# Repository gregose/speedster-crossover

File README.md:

# Speedster Crossover

Crossover PCB layout for [Paul Carmody's Speedster speakers](https://sites.google.com/site/undefinition/speedster). Designed with V-cut stackable boards for high and low-pass circuits.

### Render

### Schematic

### BOM

The layout was designed for the following components. Extra pads have been added to allow the use of physically smaller capacitors. Additional pins have been added to X1 and X2 to support the use of through-hole quick disconnects.

Ref | Component | Link 
----| --------- | -------------
R1  | Vishay Mills MRA-12 10R | http://www.digikey.com/product-search/en?mpart=MRA-1210R00FE12&vendor=541
R2  | Vishay Mills MRA-12 8R | http://www.digikey.com/product-search/en?mpart=MRA-128R000FE12&vendor=541
C1  | AUDYN CAP PLUS MKP 2.20 MF/ 800 V 2% AXIAL 43X25 | https://www.intertechnik.com/Shop/Cross-over-parts/Capacitors/Audyn-Cap-Plus/_PLUS22008_1768,en,280,46735
C2  | AUDYN CAP PLUS MKP 4.70 MF/ 800 V 2% AXIAL 63X35 | https://www.intertechnik.com/Shop/Cross-over-parts/Capacitors/Audyn-Cap-Plus/_PLUS47008_1768,en,280,46738
C3  | AUDYN CAP PLUS MKP 4.70 MF/ 800 V 2% AXIAL 63X35 | https://www.intertechnik.com/Shop/Cross-over-parts/Capacitors/Audyn-Cap-Plus/_PLUS47008_1768,en,280,46738
L1  | Meniscus Audio .25mH, Perfect Layer 20ga. | http://meniscusaudio.com/025mh-20ga-p-597.html
L2  | Meniscus Audio 1.5mH, Layer  Wound 18ga. | http://meniscusaudio.com/150mh-18-ga-p-638.html
L3  | Meniscus Audio .35mH, Layer  Wound 18ga. | http://meniscusaudio.com/035mh-18-ga-p-622.html
X1  | Phoenix Contact 1730418 (CONN TERM BLOCK 4POS 5.08MM) | http://www.digikey.com/product-search/en?mpart=1730418&vendor=277
X2  | Phoenix Contact 1730434 (CONN TERM BLOCK 6POS 5.08MM) | http://www.digikey.com/product-search/en?mpart=1730434&vendor=277
X1/2 Alt. | PCB quick disconnect terminal | http://www.mcmaster.com/#7956k5/=10cwxu4

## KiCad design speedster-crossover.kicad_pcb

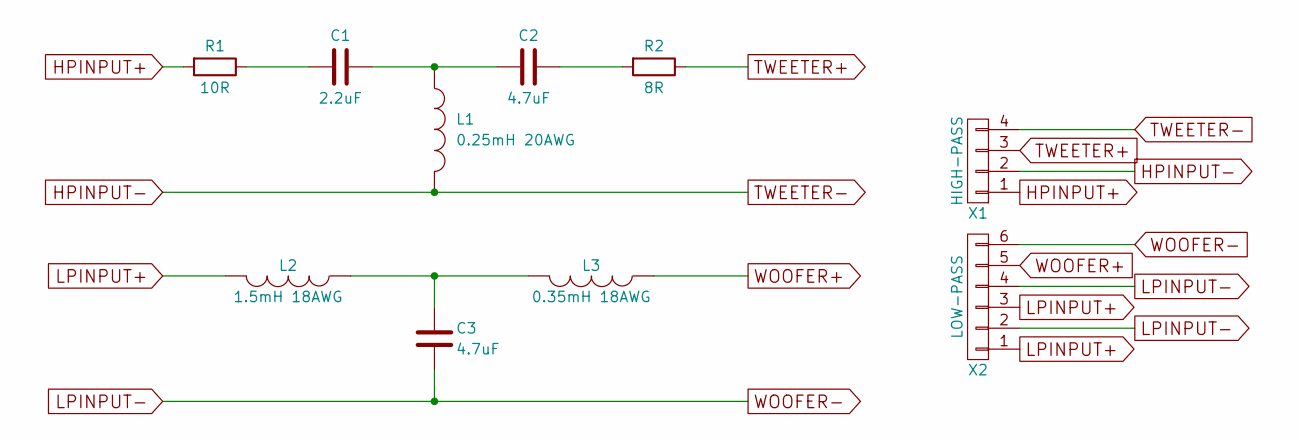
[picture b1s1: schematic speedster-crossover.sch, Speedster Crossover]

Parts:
C1: 2.2uF; OAL_cap_2.2
C2, C3: 4.7uF; OAL_cap_4.7
L1: 0.25mH 20AWG; OAL_inductor_0.25-20AWG-Vertical
L2: 1.5mH 18AWG; OAL_inductor_1.5-18AWG
L3: 0.35mH 18AWG; OAL_inductor_0.35-18AWG-Vertical
R1: 10R; OAL_resistor_MRA12
R2: 8R; OAL_resistor_MRA12
X1: HIGH-PASS; OAL_pheonix_mkds_2.5-4pos
X2: LOW-PASS; OAL_pheonix_mkds_2.5-6pos

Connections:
HPINPUT+: R1.2, X1.1
HPINPUT-: L1.2, X1.2, X1.4
LPINPUT+: L2.2, X2.1, X2.3
LPINPUT-: C3.2, X2.2, X2.4, X2.6
unnamed: C1.1, C2.1, L1.1
unnamed: C1.2, R1.1
unnamed: C2.2, R2.2
unnamed: C3.1, L2.1, L3.2
TWEETER+: R2.1, X1.3
WOOFER+: L3.1, X2.5

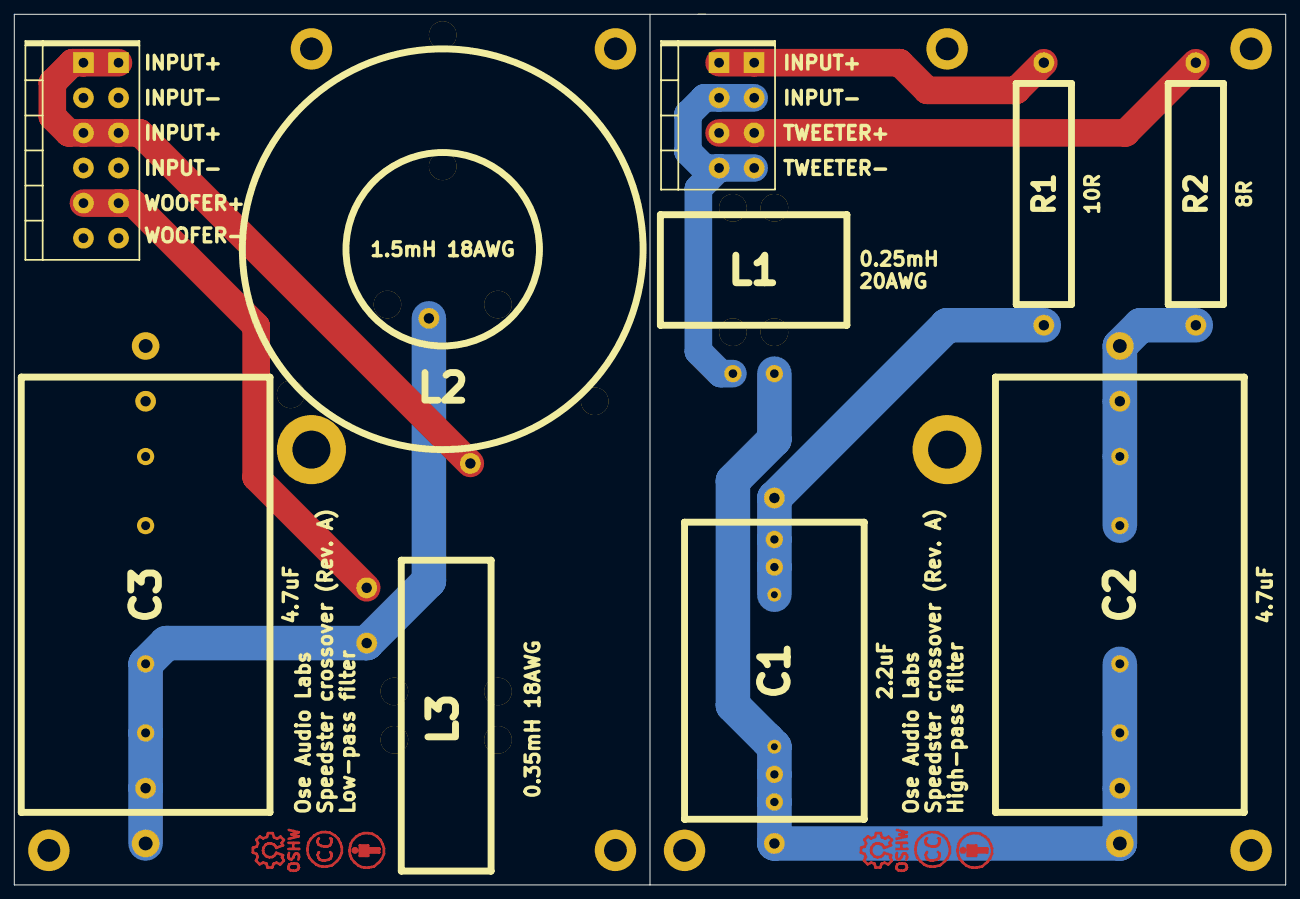
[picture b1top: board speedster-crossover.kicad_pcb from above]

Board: 2 copper layers, 184.0 x 126.0 mm, 10 parts (0 on the bottom side), 10 nets.

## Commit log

2015-12-17 initial layout
2015-12-17 some 3d renders
2015-12-17 Add details
2015-12-17 add schematic image
2015-12-17 Fix digikey links
2015-12-23 Updates to layout
    - smaller L3 footprint
    - tighter C1 lead spacing
    - alternative quick-disconnect pins for X1/2
    (http://www.mcmaster.com/#7956k5/=10cwxu4)
    - plated mounting holes
2015-12-23 Mention PCB quick disconnect alts
2015-12-23 Fine tune some lead spacing, back silkscreen logo
2015-12-26 add license, update logos
2015-12-28 final tweaks before fab
